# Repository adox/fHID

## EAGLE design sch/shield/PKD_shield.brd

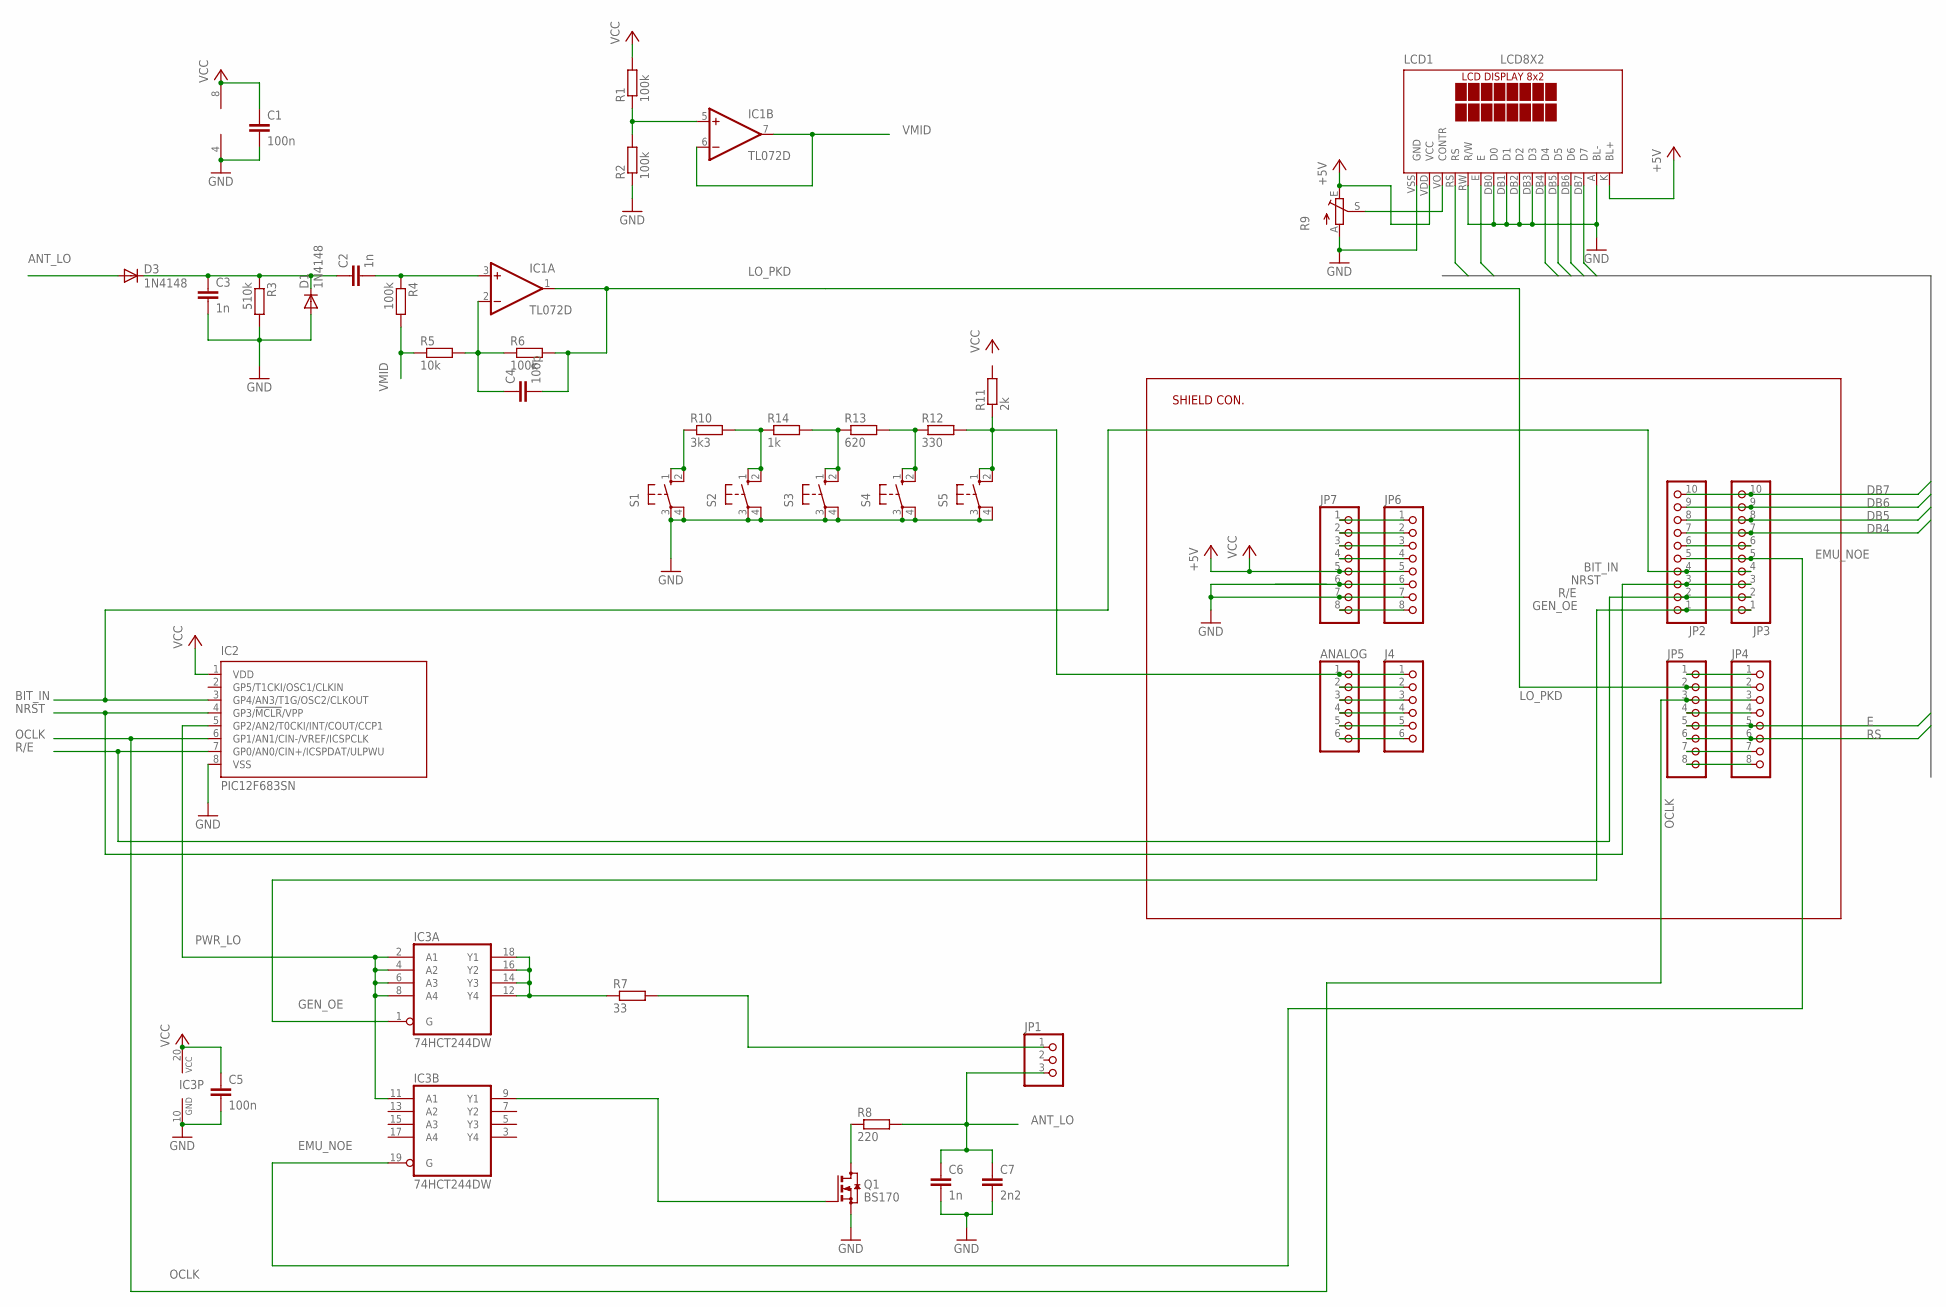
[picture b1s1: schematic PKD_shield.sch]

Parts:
ANALOG: PINHD-1X6; 1X06
C1, C5: 100n; C1206
C2, C3, C6: 1n; C1206
C4: 100p; C1206
C7: 2n2; C1206
D1, D3: 1N4148; MELF-MLL41
IC1: TL072D; SO08
IC2: PIC12F683SN; SO-08; MPN PIC12F683-I/SN
IC3: 74HCT244DW; SO20W
J4: PINHD-1X6; 1X06
JP1: PINHD-1X3; 1X03
JP2, JP3: PINHD-1X10; 1X10
JP4, JP5, JP6, JP7: PINHD-1X8; 1X08
LCD1: LCD8X2
Q1: BS170; TO92
R1, R2, R4, R6: 100k; R1206
R3: 510k; R1206
R5: 10k; R1206
R7: 33; R1206
R8: 220; R1206
R9: TRIM_EU-B25P; B25P
R10: 3k3; R1206
R11: 2k; R1206
R12: 330; R1206
R13: 620; R1206
R14: 1k; R1206
S1, S2, S3, S4, S5: 10-XX; B3F-10XX

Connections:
+5V: LCD1.K (BL+), LCD1.VDD (VCC), R9.E
+9V: JP6.8, JP7.8
ANT_LO: C6.1, C7.1, D3.A, JP1.3, R8.2
BIT_IN: IC2.3 (GP4/AN3/T1G/OSC2/CLKOUT), JP2.4, JP3.4
DB4: JP2.7, JP3.7, LCD1.DB4 (D4)
DB5: JP2.8, JP3.8, LCD1.DB5 (D5)
DB6: JP2.9, JP3.9, LCD1.DB6 (D6)
DB7: JP2.10, JP3.10, LCD1.DB7 (D7)
E: JP4.5, JP5.5, LCD1.E
EMU_NOE: IC3.19 (G), JP2.5, JP3.5
GEN_OE: IC3.1 (G), JP2.1, JP3.1
GND: C1.2, C3.2, C5.2, C6.2, C7.2, D1.A, IC1.4 (V-), IC2.8 (VSS), IC3.10 (GND), JP6.7, JP7.7, LCD1.A (BL-), LCD1.DB0 (D0), LCD1.DB1 (D1), LCD1.DB2 (D2), LCD1.DB3 (D3), LCD1.RW (R/W), LCD1.VSS (GND), Q1.3 (S), R2.1, R3.2, R9.A, S1.3, S1.4 (P1), S2.3, S2.4 (P1), S3.3, S3.4 (P1), S4.3, S4.4 (P1), S5.3, S5.4 (P1)
LO_PKD: JP4.2, JP5.2
LO_PKD_U: C4.2, IC1.1 (OUT), R6.2
unnamed: JP6.3, JP7.3
unnamed: LCD1.VO (CONTR), R9.S
unnamed: JP2.6, JP3.6
unnamed: IC3.9 (Y1), Q1.2 (G)
unnamed: R10.1, S1.1 (S), S1.2 (S1)
unnamed: R10.2, R14.1, S2.1 (S), S2.2 (S1)
unnamed: JP4.1, JP5.1
unnamed: R13.1, R14.2, S3.1 (S), S3.2 (S1)
unnamed: R12.1, R13.2, S4.1 (S), S4.2 (S1)
unnamed: JP4.4, JP5.4
unnamed: JP4.7, JP5.7
unnamed: JP4.8, JP5.8
unnamed: IC1.5 (+IN), R1.1, R2.2
unnamed: C2.1, C3.1, D1.C, D3.C, R3.1
unnamed: ANALOG.1, J4.1, R11.1, R12.2, S5.1 (S), S5.2 (S1)
unnamed: ANALOG.2, J4.2
unnamed: ANALOG.3, J4.3
unnamed: ANALOG.4, J4.4
unnamed: ANALOG.5, J4.5
unnamed: ANALOG.6, J4.6
unnamed: JP6.6, JP7.6
unnamed: C2.2, IC1.3 (+IN), R4.1
unnamed: C4.1, IC1.2 (-IN), R5.2, R6.1
unnamed: JP1.1, R7.2
unnamed: IC3.12 (Y4), IC3.14 (Y3), IC3.16 (Y2), IC3.18 (Y1), R7.1
unnamed: JP6.2, JP7.2
unnamed: JP6.1, JP7.1
unnamed: Q1.1 (D), R8.1
unnamed: JP6.4, JP7.4
NRST: IC2.4 (GP3/!MCLR!/VPP), JP2.3, JP3.3
OCLK: IC2.6 (GP1/AN1/CIN-/VREF/ICSPCLK), JP4.3, JP5.3
PWR_LO: IC2.5 (GP2/AN2/T0CKI/INT/COUT/CCP1), IC3.2 (A1), IC3.4 (A2), IC3.6 (A3), IC3.8 (A4), IC3.11 (A1)
R/E: IC2.7 (GP0/AN0/CIN+/ICSPDAT/ULPWU), JP2.2, JP3.2
RS: JP4.6, JP5.6, LCD1.RS
VCC: C1.1, C5.1, IC1.8 (V+), IC2.1 (VDD), IC3.20 (VCC), JP6.5, JP7.5, R1.2
VMID: IC1.6 (-IN), IC1.7 (OUT), R4.2, R5.1

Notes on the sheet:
SHIELD CON.

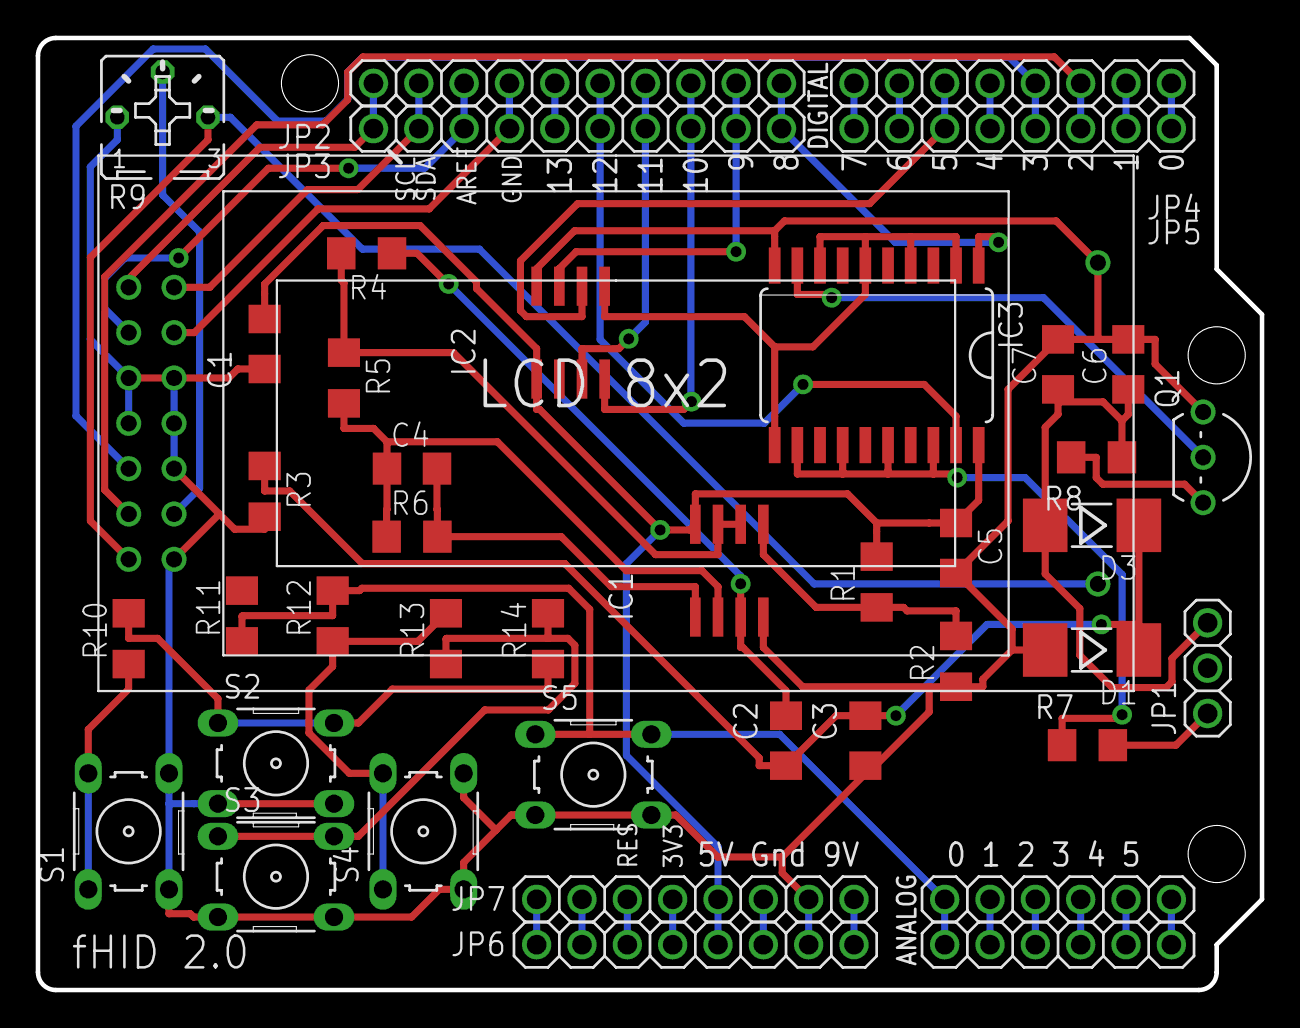
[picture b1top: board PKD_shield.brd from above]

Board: 2 copper layers, 68.6 x 53.3 mm, 42 parts (0 on the bottom side), 50 nets.

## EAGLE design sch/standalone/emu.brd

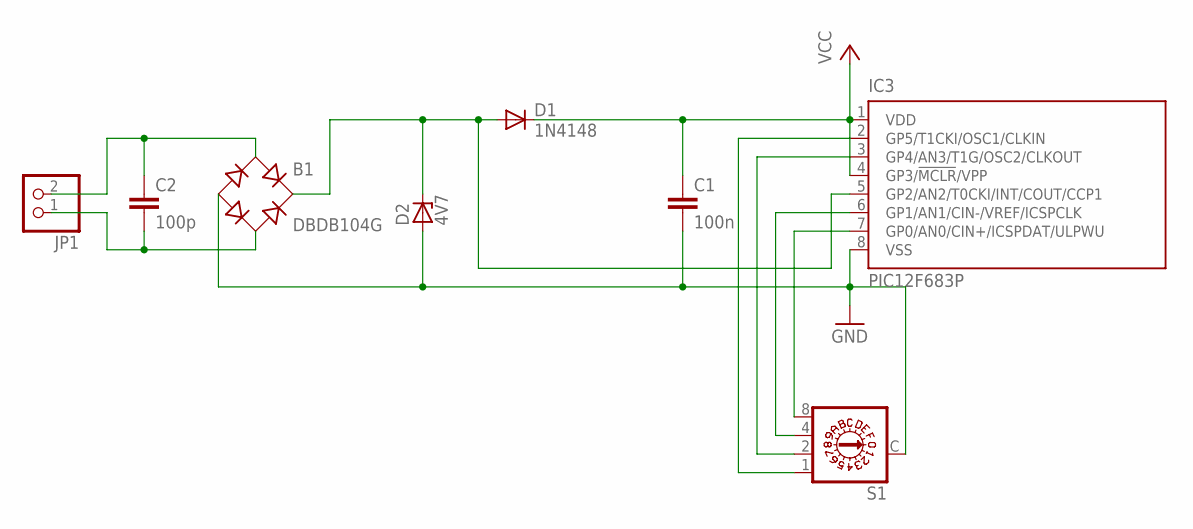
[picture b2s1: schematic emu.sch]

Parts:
B1: DBDB104G; DB
C1: 100n; C025-025X050
C2: 100p; C025-025X050
D1: 1N4148; DO35-7
D2: 4V7; ZDIO-5
IC3: PIC12F683P; DIL8
JP1: PINHD-1X2/90; 1X02/90
S1: S10HEX

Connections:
GND: B1.-, C1.2, D2.A, IC3.8 (VSS), S1.C
unnamed: B1.AC2, C2.2, JP1.1
unnamed: B1.AC1, C2.1, JP1.2
unnamed: B1.+, D1.A, D2.C, IC3.5 (GP2/AN2/T0CKI/INT/COUT/CCP1)
unnamed: IC3.7 (GP0/AN0/CIN+/ICSPDAT/ULPWU), S1.8
unnamed: IC3.6 (GP1/AN1/CIN-/VREF/ICSPCLK), S1.4
unnamed: IC3.3 (GP4/AN3/T1G/OSC2/CLKOUT), S1.2
unnamed: IC3.2 (GP5/T1CKI/OSC1/CLKIN), S1.1
VCC: C1.1, D1.C, IC3.1 (VDD), IC3.4 (GP3/!MCLR!/VPP)

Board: 2 copper layers, 8 parts (0 on the bottom side), 9 nets, no tracks yet.

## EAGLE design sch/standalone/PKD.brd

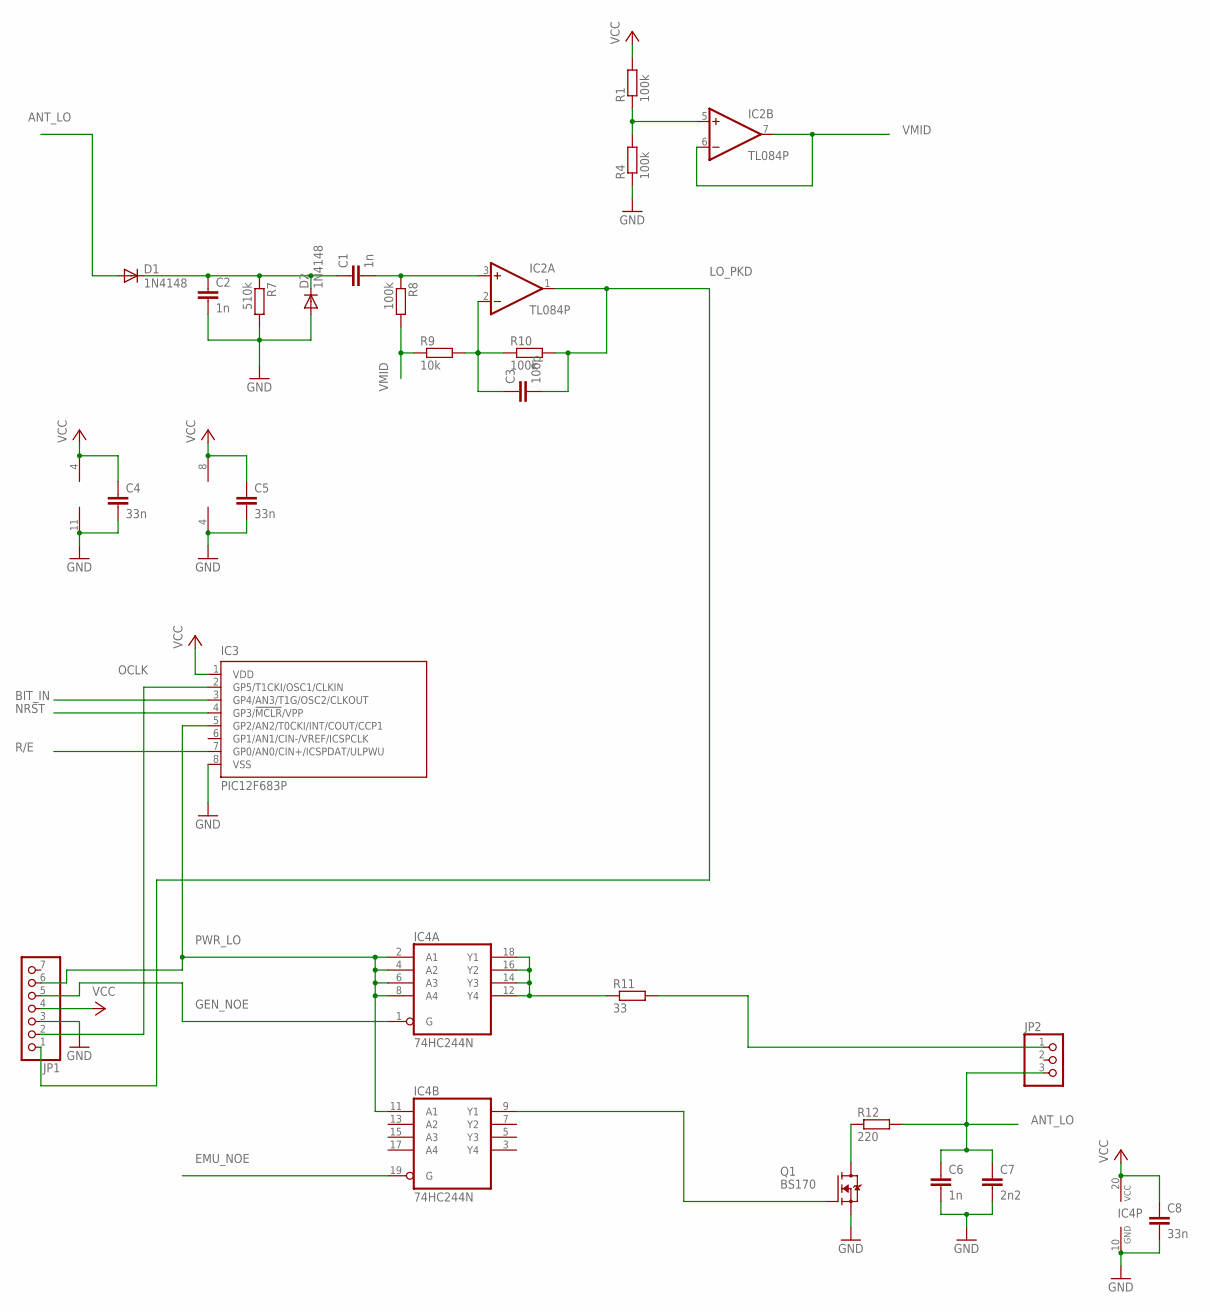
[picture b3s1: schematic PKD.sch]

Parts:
C1, C6: 1n; C025-025X050
C2: 1n; C050-030X075
C3: 100p; C025-025X050
C4, C5: 33n; C025-025X050
C7: 2n2; C025-025X050
C8: 33n; C050-030X075
D1, D2: 1N4148; DO35-10
IC1: LM393N; DIL08
IC2: TL084P; DIL14
IC3: PIC12F683P; DIL8
IC4: 74HC244N; DIL20
JP1: PINHD-1X7; 1X07
JP2: PINHD-1X3/90; 1X03/90
Q1: BS170; TO92-
R1, R4, R8, R10: 100k; 0207/10
R7: 510k; 0207/10
R9: 10k; 0207/10
R11: 33; 0207/10
R12: 220; 0207/10

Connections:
ANT_LO: C6.1, C7.1, D1.A, JP2.3, R12.2
BIT_IN: IC3.3 (GP4/AN3/T1G/OSC2/CLKOUT)
EMU_NOE: IC4.19 (G)
GEN_NOE: IC4.1 (G), JP1.5
GND: C2.2, C4.2, C5.2, C6.2, C7.2, C8.2, D2.A, IC1.4 (V-), IC2.11 (V-), IC3.8 (VSS), IC4.10 (GND), JP1.3, Q1.3 (S), R4.1, R7.2
LO_PKD: C3.2, IC2.1 (OUT), JP1.1, R10.2
unnamed: C1.1, C2.1, D1.C, D2.C, R7.1
unnamed: C1.2, IC2.3 (+IN), R8.1
unnamed: IC2.5 (+IN), R1.1, R4.2
unnamed: Q1.1 (D), R12.1
unnamed: C3.1, IC2.2 (-IN), R9.2, R10.1
unnamed: IC4.9 (Y1), Q1.2 (G)
unnamed: JP2.1, R11.2
unnamed: IC4.12 (Y4), IC4.14 (Y3), IC4.16 (Y2), IC4.18 (Y1), R11.1
NRST: IC3.4 (GP3/!MCLR!/VPP)
OCLK: IC3.2 (GP5/T1CKI/OSC1/CLKIN), JP1.2
PWR_LO: IC3.5 (GP2/AN2/T0CKI/INT/COUT/CCP1), IC4.2 (A1), IC4.4 (A2), IC4.6 (A3), IC4.8 (A4), IC4.11 (A1), JP1.6
R/E: IC3.7 (GP0/AN0/CIN+/ICSPDAT/ULPWU)
VCC: C4.1, C5.1, C8.1, IC1.8 (V+), IC2.4 (V+), IC3.1 (VDD), IC4.20 (VCC), JP1.4, R1.2
VMID: IC2.6 (-IN), IC2.7 (OUT), R8.2, R9.1

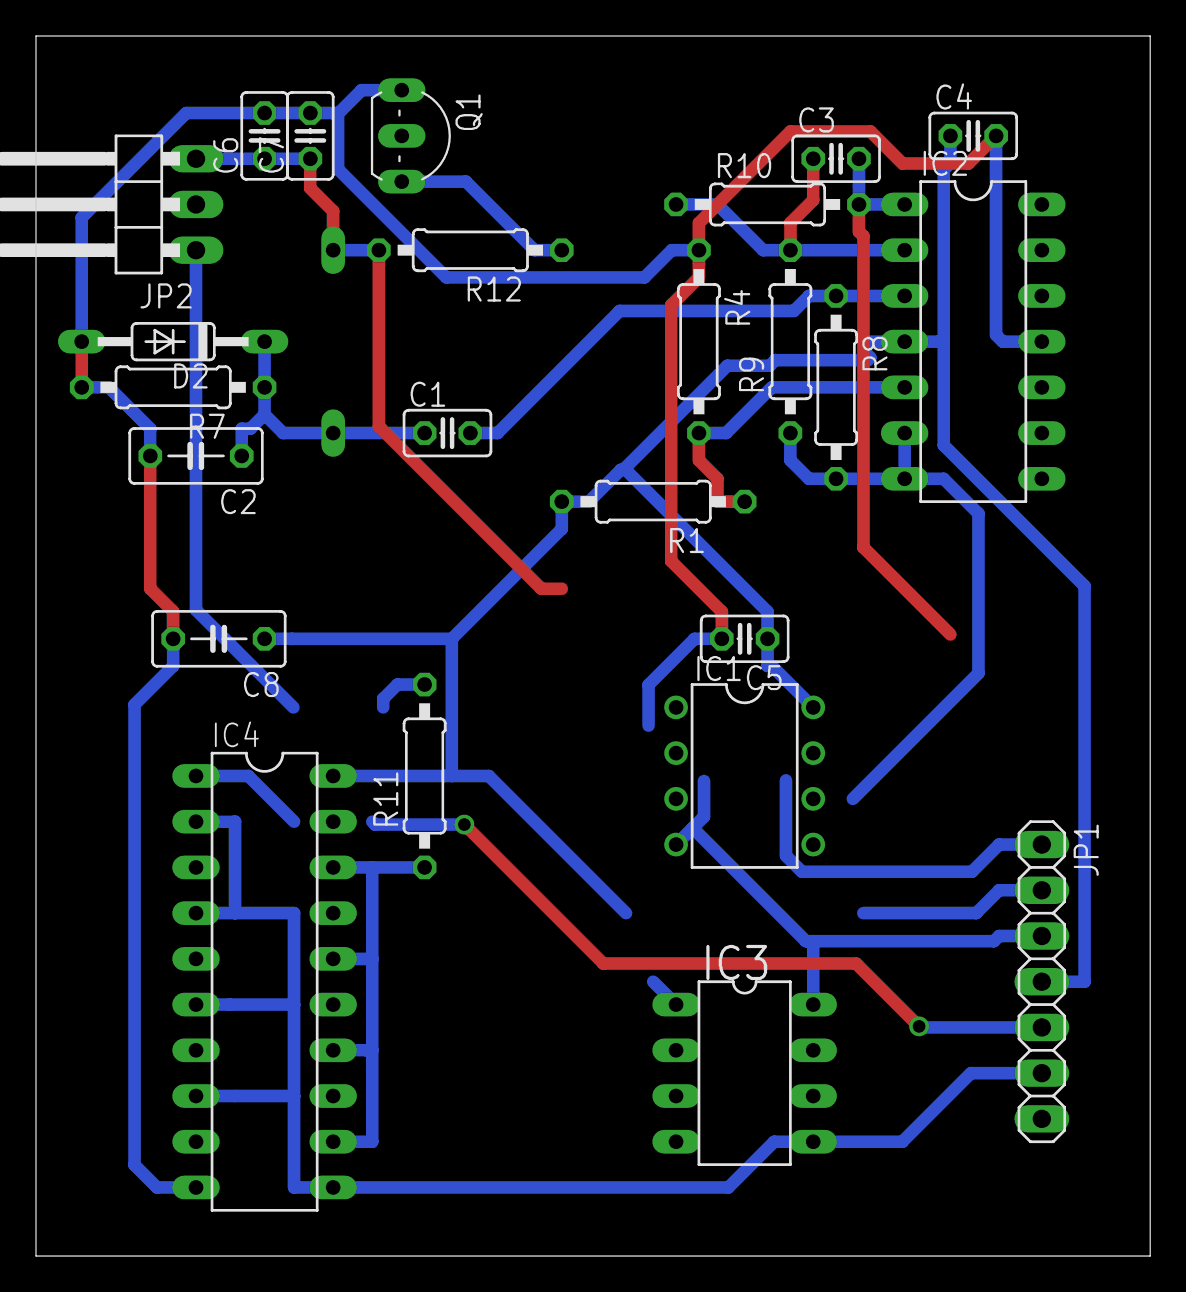
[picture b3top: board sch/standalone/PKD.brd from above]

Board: 2 copper layers, 61.9 x 67.8 mm, 25 parts (1 on the bottom side), 16 nets.

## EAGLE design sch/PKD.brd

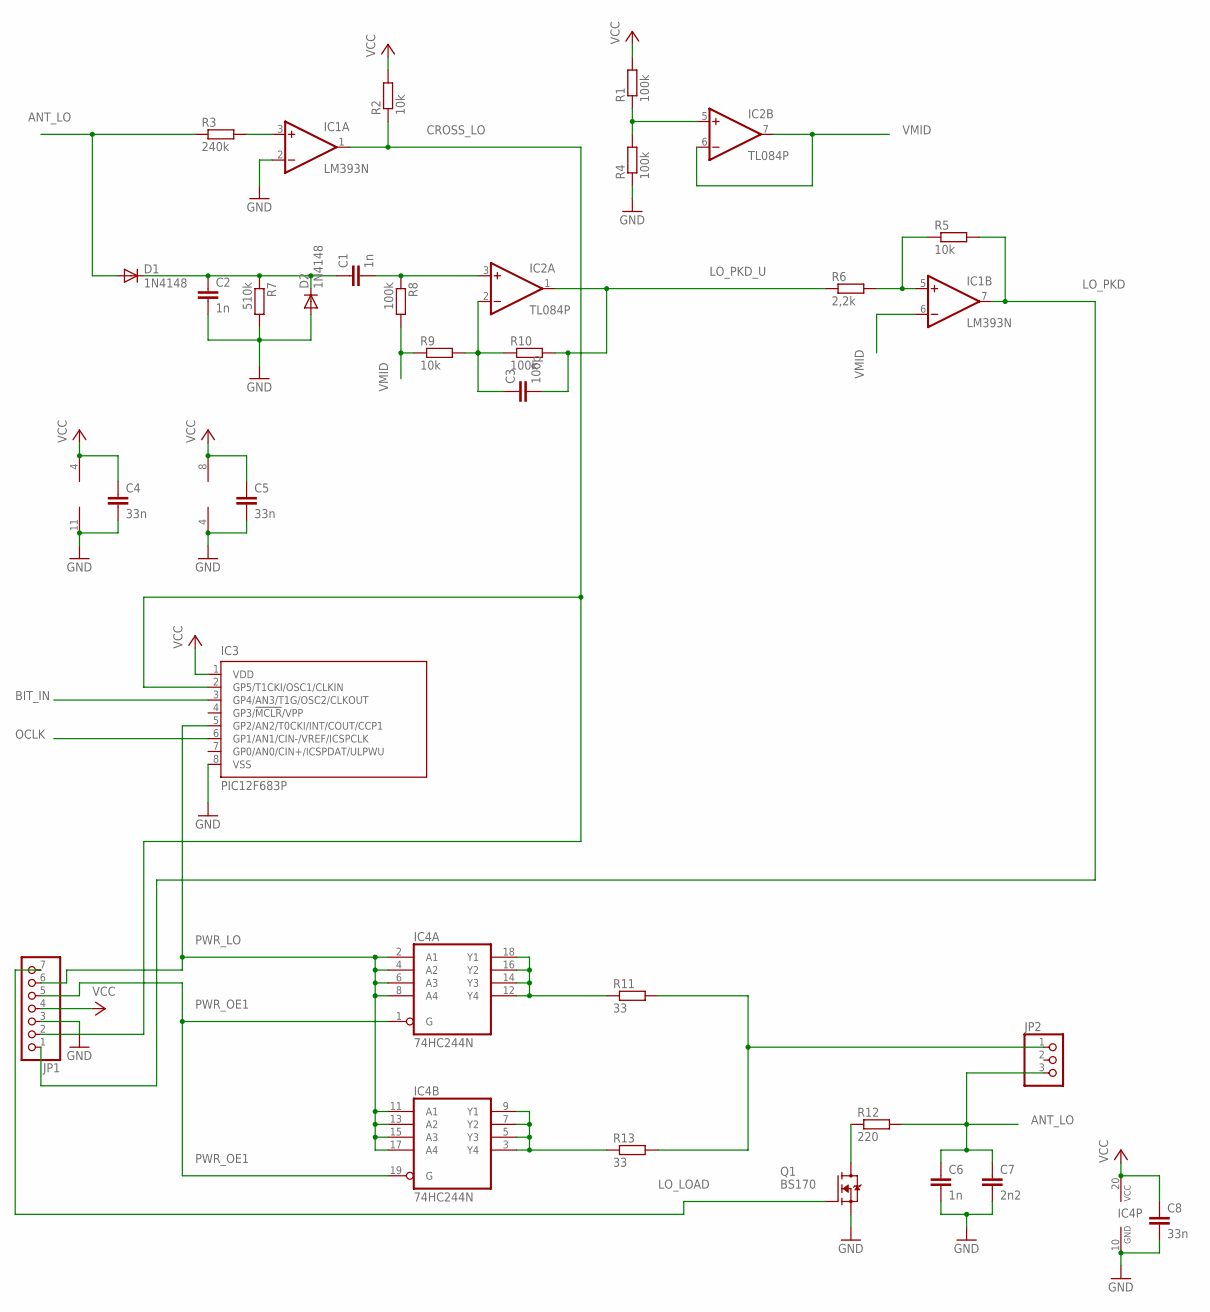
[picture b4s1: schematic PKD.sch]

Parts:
C1, C6: 1n; C025-025X050
C2: 1n; C050-030X075
C3: 100p; C025-025X050
C4, C5: 33n; C025-025X050
C7: 2n2; C025-025X050
C8: 33n; C050-030X075
D1, D2: 1N4148; DO35-10
IC1: LM393N; DIL08
IC2: TL084P; DIL14
IC3: PIC12F683P; DIL8
IC4: 74HC244N; DIL20
JP1: PINHD-1X7; 1X07
JP2: PINHD-1X3/90; 1X03/90
Q1: BS170; TO92-
R1, R4, R8, R10: 100k; 0207/10
R2, R5, R9: 10k; 0207/10
R3: 240k; 0207/10
R6: 2,2k; 0207/10
R7: 510k; 0207/10
R11, R13: 33; 0207/10
R12: 220; 0207/10

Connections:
ANT_LO: C6.1, C7.1, D1.A, JP2.3, R3.1, R12.2
BIT_IN: IC3.3 (GP4/AN3/T1G/OSC2/CLKOUT)
CROSS_LO: IC1.1 (OUT), IC3.2 (GP5/T1CKI/OSC1/CLKIN), JP1.2, R2.1
GND: C2.2, C4.2, C5.2, C6.2, C7.2, C8.2, D2.A, IC1.2 (-IN), IC1.4 (V-), IC2.11 (V-), IC3.8 (VSS), IC4.10 (GND), JP1.3, Q1.3 (S), R4.1, R7.2
LO_LOAD: JP1.7, Q1.2 (G)
LO_PKD: IC1.7 (OUT), JP1.1, R5.2
LO_PKD_U: C3.2, IC2.1 (OUT), R6.1, R10.2
unnamed: C1.1, C2.1, D1.C, D2.C, R7.1
unnamed: C1.2, IC2.3 (+IN), R8.1
unnamed: IC2.5 (+IN), R1.1, R4.2
unnamed: Q1.1 (D), R12.1
unnamed: C3.1, IC2.2 (-IN), R9.2, R10.1
unnamed: IC1.3 (+IN), R3.2
unnamed: JP2.1, R11.2, R13.2
unnamed: IC4.12 (Y4), IC4.14 (Y3), IC4.16 (Y2), IC4.18 (Y1), R11.1
unnamed: IC4.3 (Y4), IC4.5 (Y3), IC4.7 (Y2), IC4.9 (Y1), R13.1
unnamed: IC1.5 (+IN), R5.1, R6.2
OCLK: IC3.6 (GP1/AN1/CIN-/VREF/ICSPCLK)
PWR_LO: IC3.5 (GP2/AN2/T0CKI/INT/COUT/CCP1), IC4.2 (A1), IC4.4 (A2), IC4.6 (A3), IC4.8 (A4), IC4.11 (A1), IC4.13 (A2), IC4.15 (A3), IC4.17 (A4), JP1.6
PWR_OE1: IC4.1 (G), IC4.19 (G), JP1.5
VCC: C4.1, C5.1, C8.1, IC1.8 (V+), IC2.4 (V+), IC3.1 (VDD), IC4.20 (VCC), JP1.4, R1.2, R2.2
VMID: IC1.6 (-IN), IC2.6 (-IN), IC2.7 (OUT), R8.2, R9.1

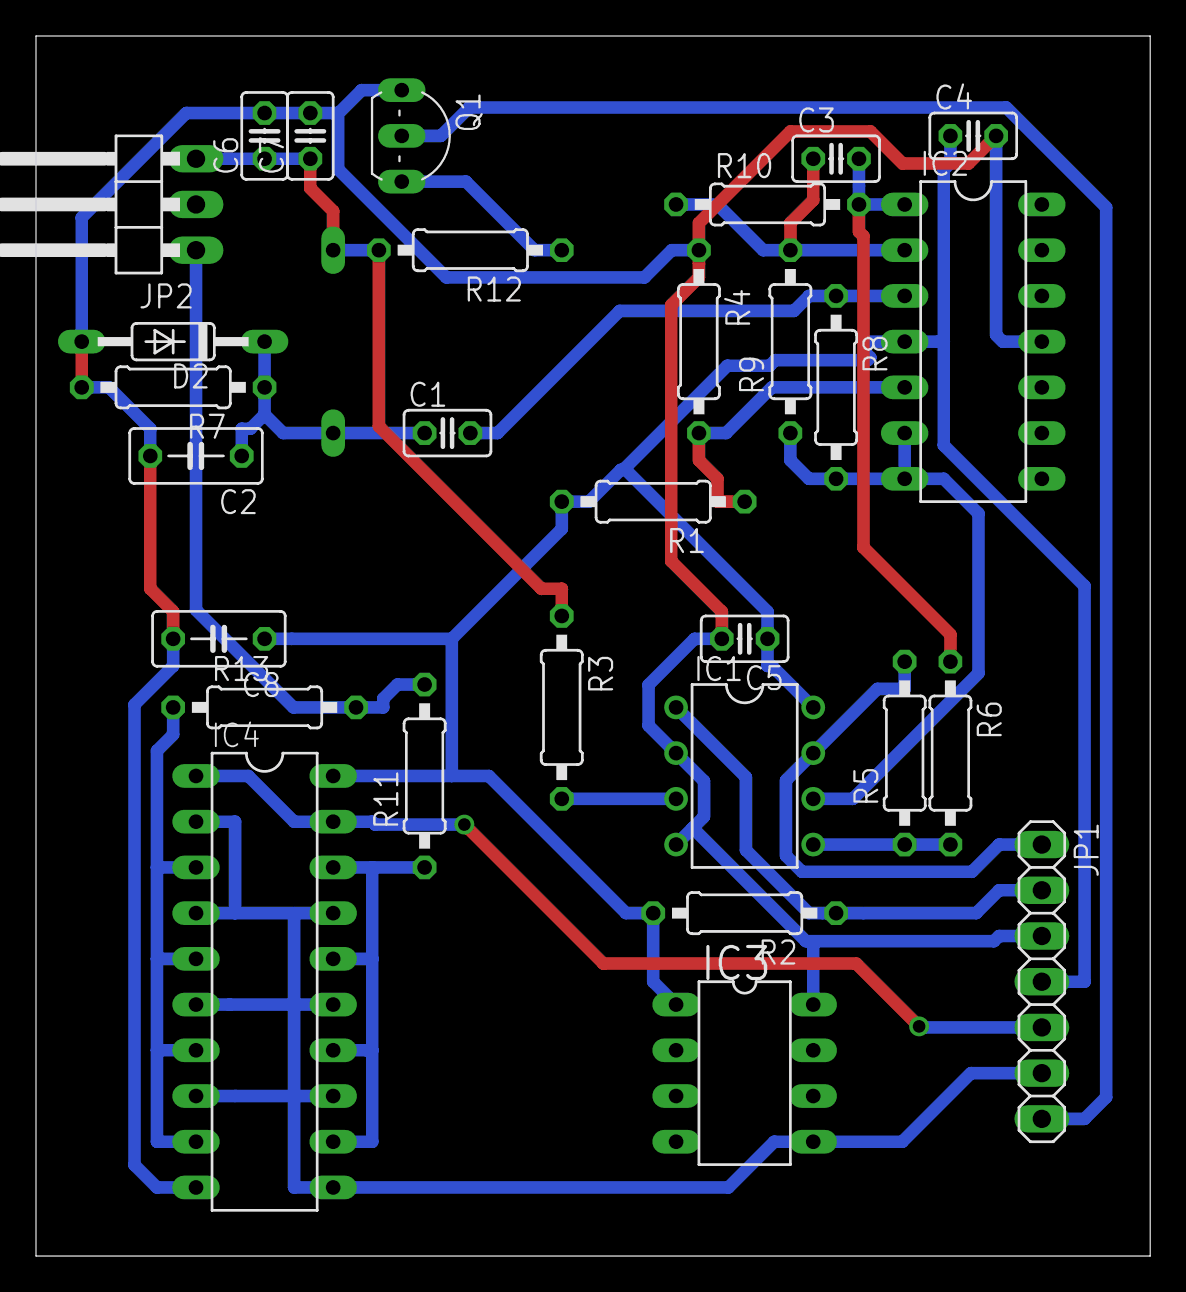
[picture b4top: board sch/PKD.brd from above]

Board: 2 copper layers, 61.9 x 67.8 mm, 30 parts (1 on the bottom side), 20 nets.

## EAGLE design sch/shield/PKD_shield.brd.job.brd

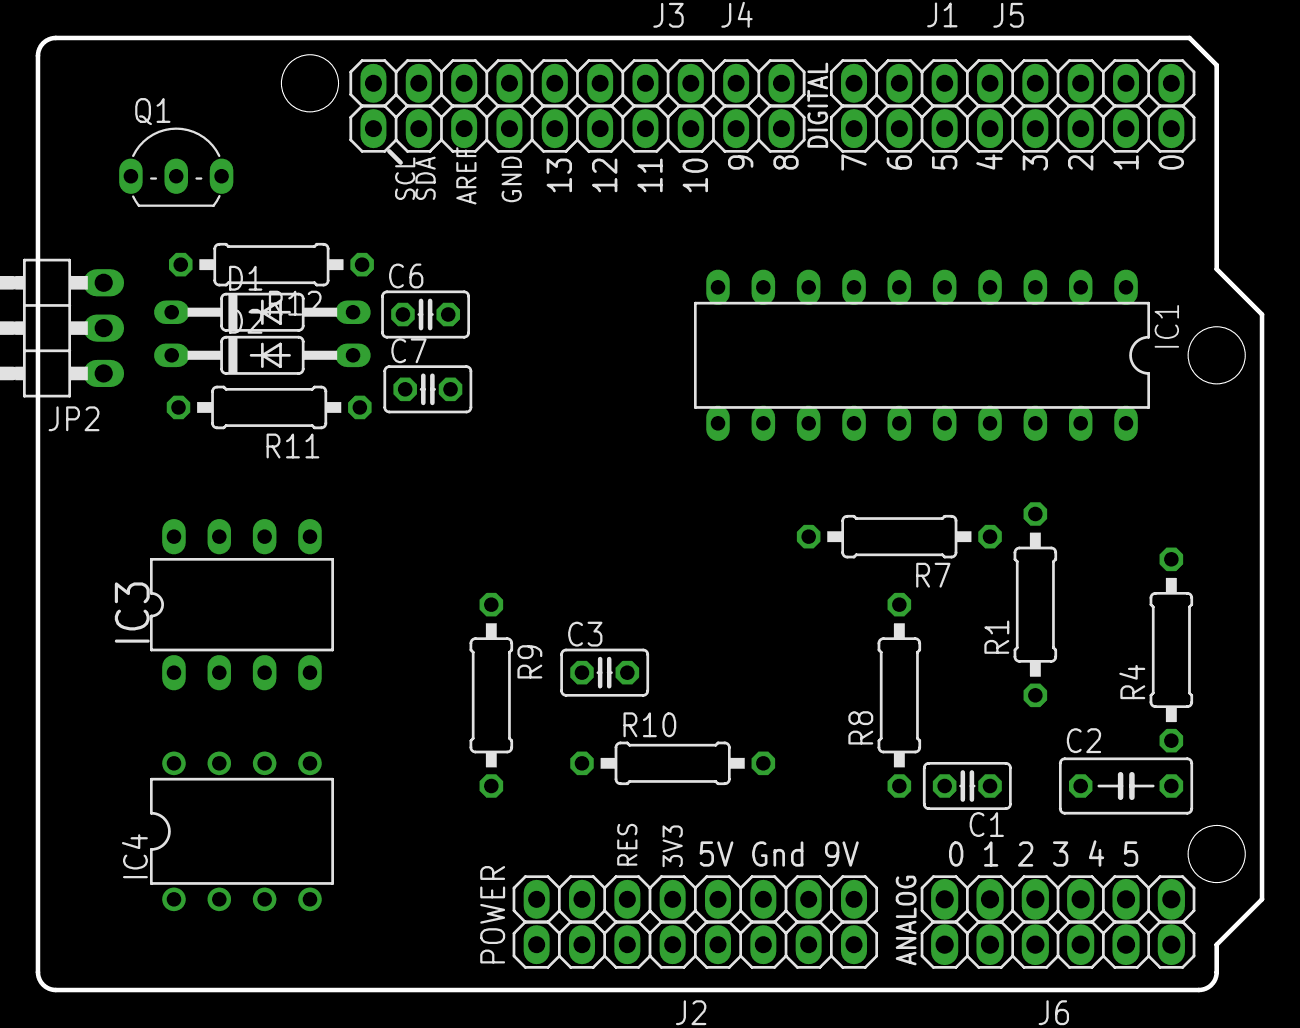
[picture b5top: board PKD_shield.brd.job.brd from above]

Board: 2 copper layers, 68.6 x 53.3 mm, 28 parts (0 on the bottom side), 44 nets, no tracks yet.

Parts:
ANALOG: 1X06
C1, C6: 1n; C025-025X050
C2: 1n; C050-030X075
C3: 100p; C025-025X050
C7: 2n2; C025-025X050
D1, D2: 1N4148; DO35-10
IC1: 74HCT244N; DIL20
IC3: PIC12F683P; DIL8
IC4: TL072P; DIL08
J1, J2, J5: 1X08-TH
J3, J4: 1X10-TH
J6: 1X06
JP2: 1X03/90
POWER: 1X08-TH
Q1: BS170; TO92-
R1, R4, R8, R10: 100k; 0207/10
R7: 510k; 0207/10
R9: 10k; 0207/10
R11: 33; 0207/10
R12: 220; 0207/10

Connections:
+9V: J2.8, POWER.8
ANT_LO: C6.1, C7.1, D1.A, JP2.3, R12.2
BIT_IN: IC3.3, J3.4, J4.4
EMU_NOE: IC1.19, J3.5, J4.5
GEN_OE: IC1.1, J3.1, J4.1
GND: C2.2, C6.2, C7.2, D2.A, IC1.10, IC3.8, J2.7, POWER.7, Q1.3, R4.1, R7.2
LO_PKD: J1.2, J5.2
LO_PKD_U: C3.2, IC4.1, R10.2
unnamed: J2.3, POWER.3
unnamed: J3.6, J4.6
unnamed: IC1.9, Q1.2
unnamed: J1.1, J5.1
unnamed: J1.4, J5.4
unnamed: J1.5, J5.5
unnamed: J1.6, J5.6
unnamed: J1.7, J5.7
unnamed: J1.8, J5.8
unnamed: IC4.5, R1.1, R4.2
unnamed: C1.1, C2.1, D1.C, D2.C, R7.1
unnamed: ANALOG.1, J6.1
unnamed: ANALOG.2, J6.2
unnamed: ANALOG.3, J6.3
unnamed: ANALOG.4, J6.4
unnamed: ANALOG.5, J6.5
unnamed: ANALOG.6, J6.6
unnamed: J3.7, J4.7
unnamed: J2.6, POWER.6
unnamed: C1.2, IC4.3, R8.1
unnamed: C3.1, IC4.2, R9.2, R10.1
unnamed: JP2.1, R11.2
unnamed: IC1.12, IC1.14, IC1.16, IC1.18, R11.1
unnamed: J2.2, POWER.2
unnamed: J2.1, POWER.1
unnamed: Q1.1, R12.1
unnamed: J3.9, J4.9
unnamed: J3.10, J4.10
unnamed: J3.8, J4.8
unnamed: J2.4, POWER.4
NRST: IC3.4, J3.3, J4.3
OCLK: IC3.6, J1.3, J5.3
PWR_LO: IC1.2, IC1.4, IC1.6, IC1.8, IC1.11, IC3.5
R/E: IC3.7, J3.2, J4.2
VCC: IC1.20, IC3.1, J2.5, POWER.5, R1.2
VMID: IC4.6, IC4.7, R8.2, R9.1

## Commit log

2012-06-06 BRD update
2012-06-07 Initial Arduino firmware
2012-06-07 Working intervals measure
2012-06-07 Intervals classification
2012-06-08 Functions converted to class RfidHID
2012-06-08 First output of card number
2012-06-09 Implemented parity bit check
2012-06-10 Added pic12f firmware and updated schematic
2012-06-10 First emulator function - not working
2012-06-11 First clean code without compiler errors, but probably not working
2012-06-11 Clean some code - emulator still todo
2012-06-13 Emulator update
2012-06-13 sch for standalone and shield version
2012-06-14 Standalone pic12f emulator working
2012-06-14 Reader + emulator working, modified (reduced) schematics for standalone ver
2012-06-26 Update master
2012-08-02 Updated shield sch
2012-08-02 Minor update
2012-08-03 Removed local conflicted files
2012-08-13 Hardware version 1.0
2012-08-15 3d model of v1.0 shield
2012-08-18 New 3d model for v2.0
2012-08-22 Correction of the silscreen on top side, layer tStop
